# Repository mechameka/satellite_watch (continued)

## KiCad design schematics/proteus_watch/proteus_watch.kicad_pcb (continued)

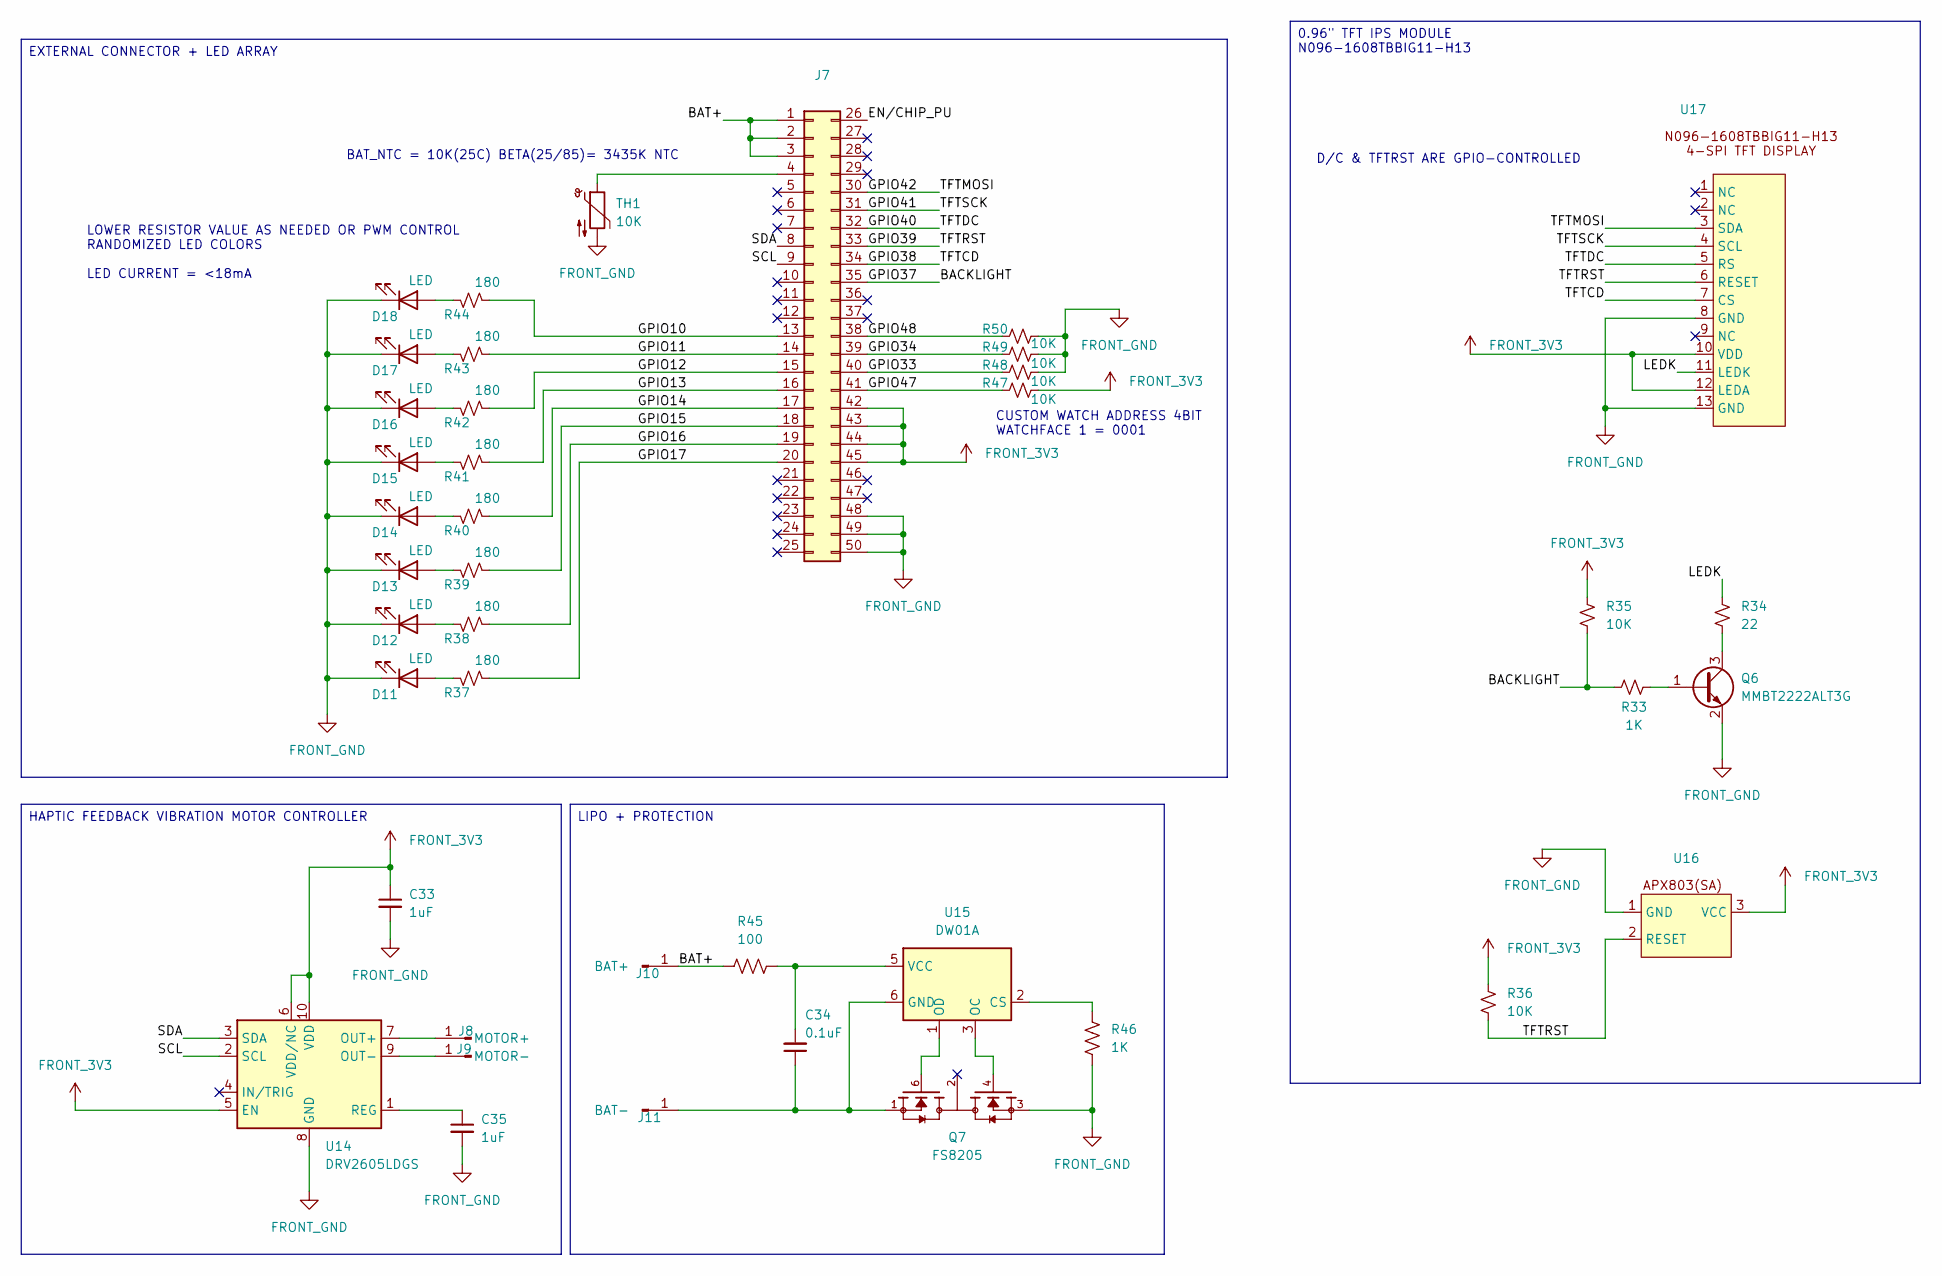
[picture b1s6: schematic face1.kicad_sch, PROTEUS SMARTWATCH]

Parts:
C33, C35: 1uF; C_0402_1005Metric_Pad0.74x0.62mm_HandSolder
C34: 0.1uF; C_0402_1005Metric_Pad0.74x0.62mm_HandSolder
D11, D12, D13, D14, D15, D16, D17, D18: LED; LED_1206_3216Metric_Pad1.42x1.75mm_HandSolder
J7: 2167010509_MOLEX; CON_2167010509_MOL
J8: MOTOR+; SolderWirePad_1x01_SMD_3x6mm
J9: MOTOR-; SolderWirePad_1x01_SMD_3x6mm
J10: BAT+; SolderWirePad_1x01_SMD_3x6mm
J11: BAT-; SolderWirePad_1x01_SMD_3x6mm
Q6: MMBT2222ALT3G; SOT-23
Q7: FS8205; SOT95P280X145-6N; PARTREV 1.9
R33, R46: 1K; R_0402_1005Metric_Pad0.72x0.64mm_HandSolder
R34: 22; R_0402_1005Metric_Pad0.72x0.64mm_HandSolder
R35, R36, R47, R48, R49, R50: 10K; R_0402_1005Metric_Pad0.72x0.64mm_HandSolder
R37, R38, R39, R40, R41, R42, R43, R44: 180; R_0402_1005Metric_Pad0.72x0.64mm_HandSolder
R45: 100; R_0402_1005Metric_Pad0.72x0.64mm_HandSolder
TH1: 10K; R_0402_1005Metric_Pad0.72x0.64mm_HandSolder
U14: DRV2605LDGS; TSSOP-10_3x3mm_P0.5mm
U15: DW01A; SOT-23-6
U16: SOT-23
U17: Wisevision N096-1608TBBIG11-H13

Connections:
/face1/BACKLIGHT: J7.35, R33.1, R35.1
/face1/BAT+: J7.1, J7.2, J7.3, J10.1 (Pin_1_1), R45.1
/face1/EN/CHIP_PU: J7.26
/face1/GPIO10: J7.13, R44.2
/face1/GPIO11: J7.14, R43.2
/face1/GPIO12: J7.15, R42.2
/face1/GPIO13: J7.16, R41.2
/face1/GPIO14: J7.17, R40.2
/face1/GPIO15: J7.18, R39.2
/face1/GPIO16: J7.19, R38.2
/face1/GPIO17: J7.20, R37.2
/face1/GPIO33: J7.40, R48.1
/face1/GPIO34: J7.39, R49.1
/face1/GPIO38: J7.34, U17.7 (CS)
/face1/GPIO39: J7.33, R36.1, U16.2 (RESET), U17.6 (RESET)
/face1/GPIO40: J7.32, U17.5 (RS)
/face1/GPIO41: J7.31, U17.4 (SCL)
/face1/GPIO42: J7.30, U17.3 (SDA)
/face1/GPIO47: J7.41, R47.1
/face1/GPIO48: J7.38, R50.1
/face1/LEDK: R34.2, U17.11 (LEDK)
/face1/SCL: J7.9, U14.2 (SCL)
/face1/SDA: J7.8, U14.3 (SDA)
FRONT_3V3: C33.1, J7.42, J7.43, J7.44, J7.45, R35.2, R36.2, R47.2, U14.5 (EN), U14.6 (VDD/NC), U14.10 (VDD), U16.3 (VCC), U17.10 (VDD), U17.12 (LEDA)
FRONT_GND: C33.2, C35.2, D11.1 (K), D12.1 (K), D13.1 (K), D14.1 (K), D15.1 (K), D16.1 (K), D17.1 (K), D18.1 (K), J7.48, J7.49, J7.50, Q6.2 (E), Q7.3, R46.1, R48.2, R49.2, R50.2, TH1.2, U14.8 (GND), U16.1 (GND), U17.8 (GND), U17.13 (GND)
unnamed: D11.2 (A), R37.1
unnamed: D12.2 (A), R38.1
unnamed: D13.2 (A), R39.1
unnamed: D14.2 (A), R40.1
unnamed: D15.2 (A), R41.1
unnamed: D16.2 (A), R42.1
unnamed: D17.2 (A), R43.1
unnamed: D18.2 (A), R44.1
unnamed: J7.4, TH1.1
unnamed: J8.1 (Pin_1_1), U14.7 (OUT+)
unnamed: J9.1 (Pin_1_1), U14.9 (OUT-)
unnamed: C34.1, J11.1 (Pin_1_1), Q7.1, U15.6 (GND)
unnamed: Q6.1 (B), R33.2
unnamed: Q6.3 (C), R34.1
unnamed: C35.1, U14.1 (REG)
unnamed: R46.2, U15.2 (CS)
unnamed: Q7.4, U15.3 (OC)
unnamed: Q7.6, U15.1 (OD)
unnamed: C34.2, R45.2, U15.5 (VCC)

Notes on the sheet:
BAT_NTC = 10K(25C) BETA(25/85)= 3435K NTC
D/C & TFTRST ARE GPIO-CONTROLLED
CUSTOM WATCH ADDRESS 4BIT WATCHFACE 1 = 0001
LOWER RESISTOR VALUE AS NEEDED OR PWM CONTROL RANDOMIZED LED COLORS LED CURRENT = <18mA
LIPO + PROTECTION
HAPTIC FEEDBACK VIBRATION MOTOR CONTROLLER
0.96" TFT IPS MODULE N096-1608TBBIG11-H13
EXTERNAL CONNECTOR + LED ARRAY

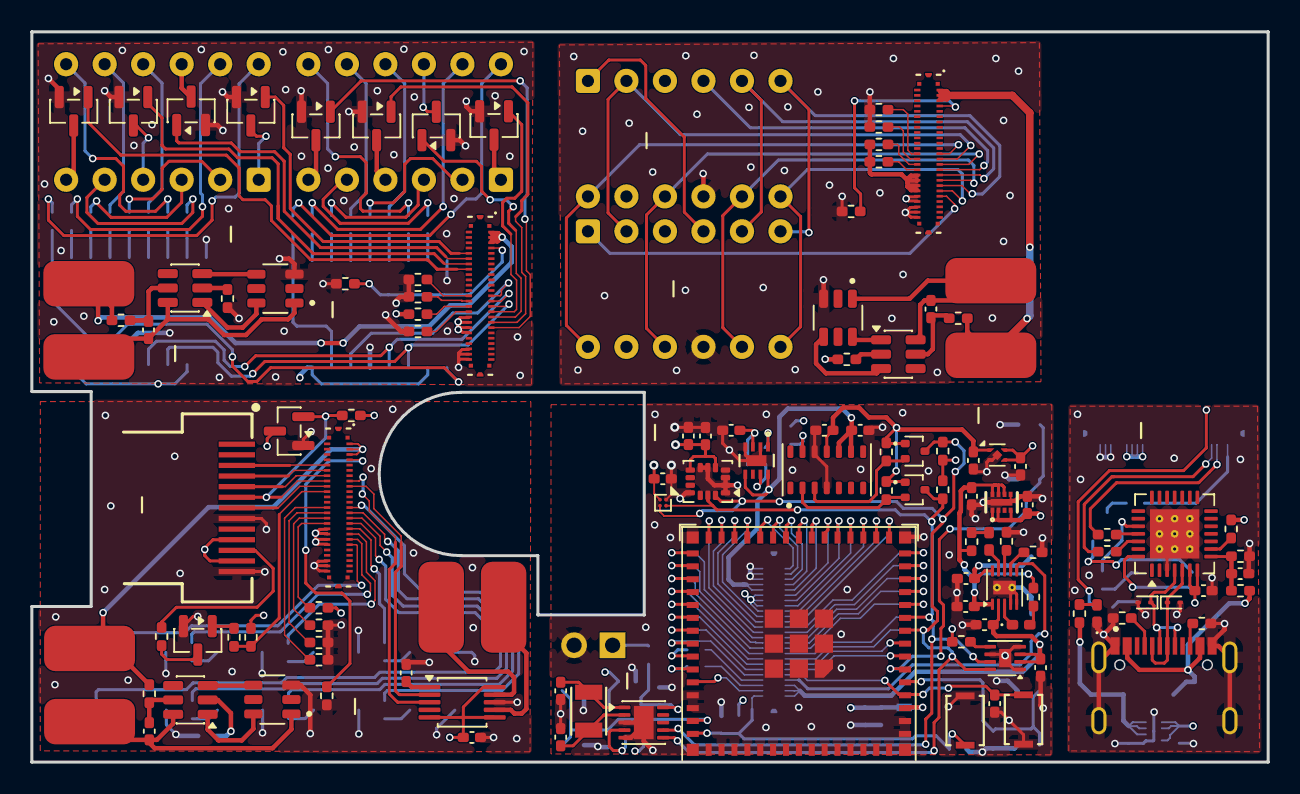
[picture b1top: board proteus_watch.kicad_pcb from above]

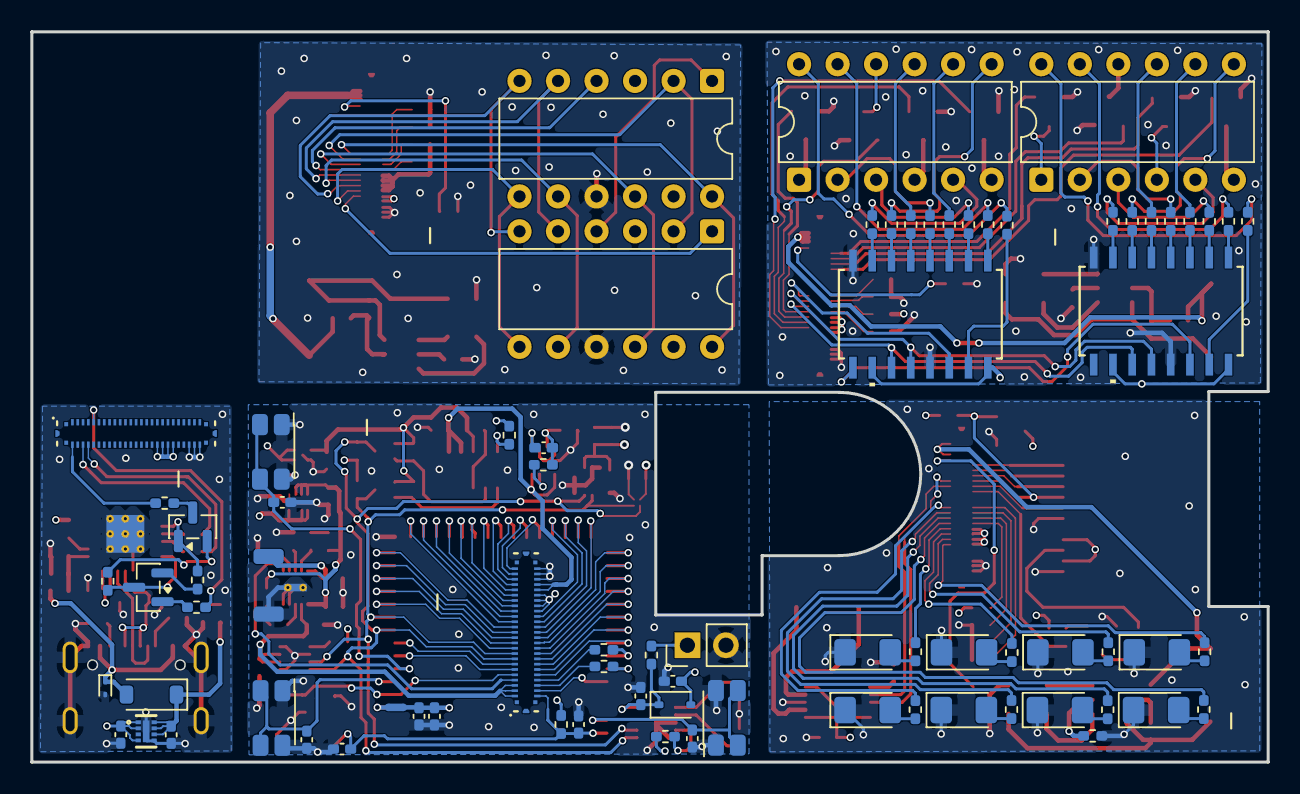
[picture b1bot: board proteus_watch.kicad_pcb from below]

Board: 4 copper layers, 81.5 x 48.2 mm, 193 parts (77 on the bottom side), 223 nets.

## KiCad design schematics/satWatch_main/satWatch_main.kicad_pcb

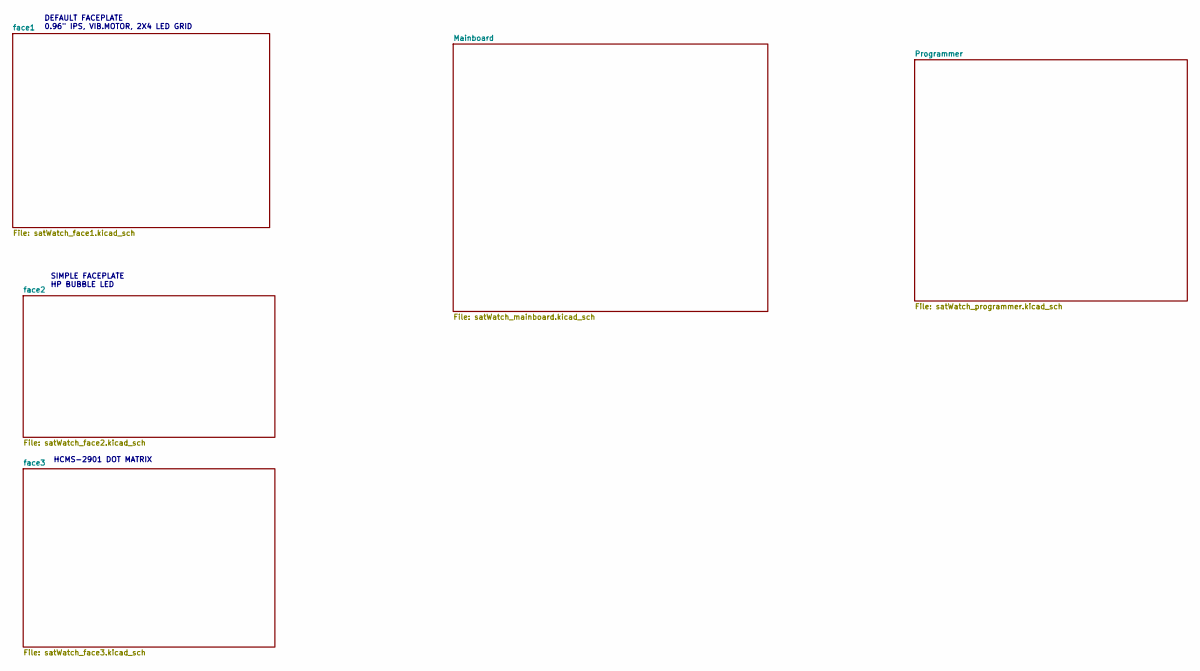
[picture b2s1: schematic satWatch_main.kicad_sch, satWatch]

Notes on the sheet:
HCMS-2901 DOT MATRIX
SIMPLE FACEPLATE HP BUBBLE LED
DEFAULT FACEPLATE 0.96" IPS, VIB.MOTOR, 2X4 LED GRID

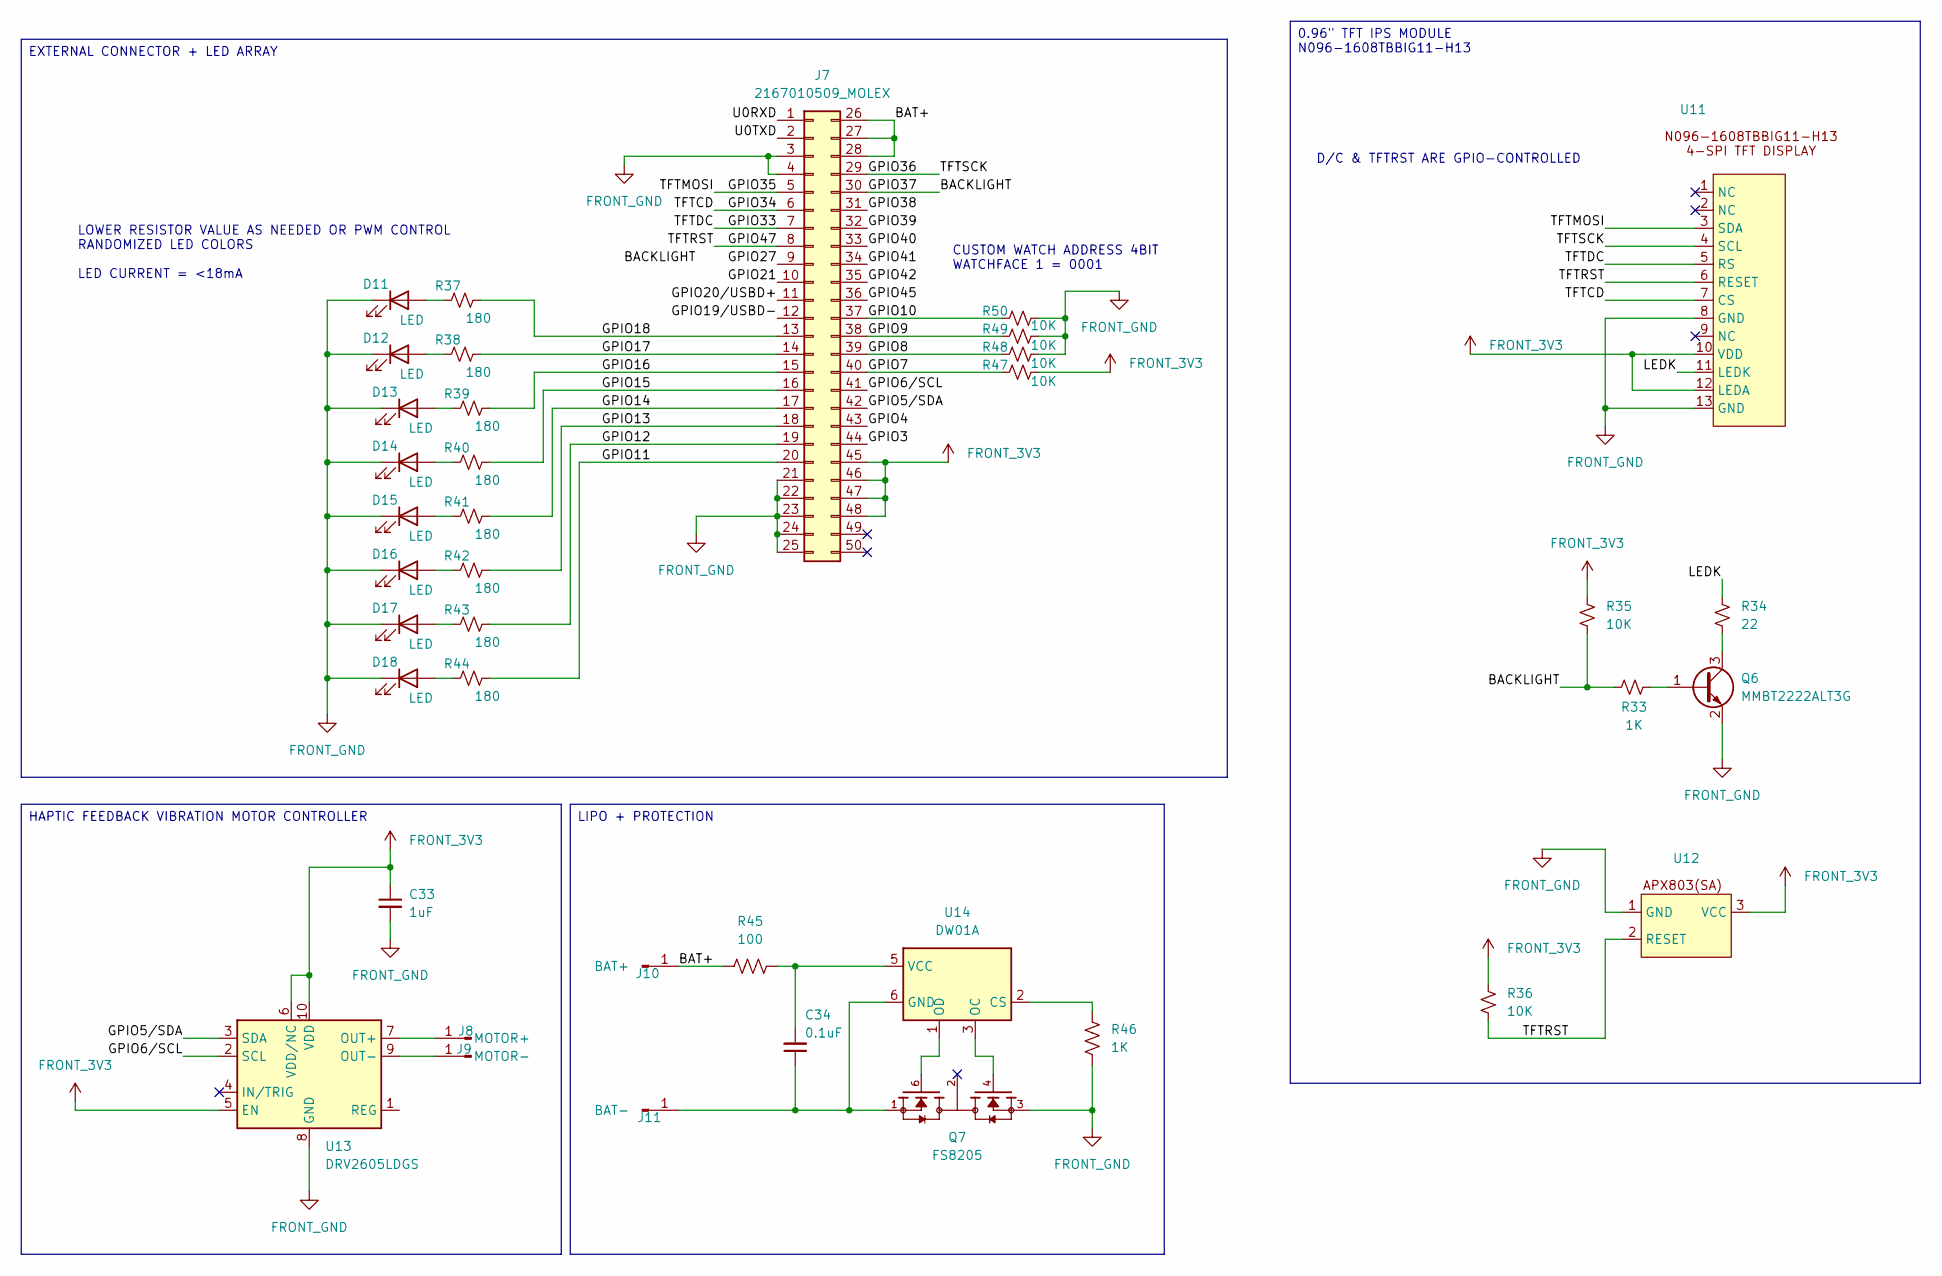
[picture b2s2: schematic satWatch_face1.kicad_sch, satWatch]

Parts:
C33: 1uF; C_0402_1005Metric_Pad0.74x0.62mm_HandSolder
C34: 0.1uF; C_0402_1005Metric_Pad0.74x0.62mm_HandSolder
D11, D12, D13, D14, D15, D16, D17, D18: LED; LED_1206_3216Metric_Pad1.42x1.75mm_HandSolder
J7: 2167010509_MOLEX; CON_2167010509_MOL
J8: MOTOR+; SolderWirePad_1x01_SMD_3x6mm
J9: MOTOR-; SolderWirePad_1x01_SMD_3x6mm
J10: BAT+; SolderWirePad_1x01_SMD_3x6mm
J11: BAT-; SolderWirePad_1x01_SMD_3x6mm
Q6: MMBT2222ALT3G; SOT-23
Q7: FS8205; SOT95P280X145-6N; PARTREV 1.9
R33, R46: 1K; R_0402_1005Metric_Pad0.72x0.64mm_HandSolder
R34: 22; R_0402_1005Metric_Pad0.72x0.64mm_HandSolder
R35, R36, R47, R48, R49, R50: 10K; R_0402_1005Metric_Pad0.72x0.64mm_HandSolder
R37, R38, R39, R40, R41, R42, R43, R44: 180; R_0402_1005Metric_Pad0.72x0.64mm_HandSolder
R45: 100; R_0402_1005Metric_Pad0.72x0.64mm_HandSolder
U11: Wisevision N096-1608TBBIG11-H13
U12: SOT-23
U13: DRV2605LDGS; TSSOP-10_3x3mm_P0.5mm
U14: DW01A; SOT-23-6

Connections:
/face1/BACKLIGHT: J7.30, R33.1, R35.1
/face1/BAT+: J7.26, J7.27, J7.28, J10.1 (Pin_1_1), R45.1
/face1/GPIO3: J7.44
/face1/GPIO4: J7.43
/face1/GPIO5/SDA: J7.42, U13.3 (SDA)
/face1/GPIO6/SCL: J7.41, U13.2 (SCL)
/face1/GPIO7: J7.40, R47.1
/face1/GPIO8: J7.39, R48.1
/face1/GPIO9: J7.38, R49.1
/face1/GPIO10: J7.37, R50.1
/face1/GPIO11: J7.20, R44.2
/face1/GPIO12: J7.19, R43.2
/face1/GPIO13: J7.18, R42.2
/face1/GPIO14: J7.17, R41.2
/face1/GPIO15: J7.16, R40.2
/face1/GPIO16: J7.15, R39.2
/face1/GPIO17: J7.14, R38.2
/face1/GPIO18: J7.13, R37.2
/face1/GPIO19/USBD-: J7.12
/face1/GPIO20/USBD+: J7.11
/face1/GPIO21: J7.10
/face1/GPIO27: J7.9
/face1/GPIO33: J7.7, U11.5 (RS)
/face1/GPIO34: J7.6, U11.7 (CS)
/face1/GPIO35: J7.5, U11.3 (SDA)
/face1/GPIO36: J7.29, U11.4 (SCL)
/face1/GPIO38: J7.31
/face1/GPIO39: J7.32
/face1/GPIO40: J7.33
/face1/GPIO41: J7.34
/face1/GPIO42: J7.35
/face1/GPIO45: J7.36
/face1/GPIO47: J7.8, R36.1, U11.6 (RESET), U12.2 (RESET)
/face1/LEDK: R34.2, U11.11 (LEDK)
/face1/U0RXD: J7.1
/face1/U0TXD: J7.2
FRONT_3V3: C33.1, J7.45, J7.46, J7.47, J7.48, R35.2, R36.2, R47.2, U11.10 (VDD), U11.12 (LEDA), U12.3 (VCC), U13.5 (EN), U13.6 (VDD/NC), U13.10 (VDD); also elsewhere on the board
FRONT_GND: C33.2, D11.1 (K), D12.1 (K), D13.1 (K), D14.1 (K), D15.1 (K), D16.1 (K), D17.1 (K), D18.1 (K), J7.3, J7.4, J7.21, J7.22, J7.23, J7.24, J7.25, Q6.2 (E), Q7.3, R46.1, R48.2, R49.2, R50.2, U11.8 (GND), U11.13 (GND), U12.1 (GND), U13.8 (GND); also elsewhere on the board
unnamed: D11.2 (A), R37.1
unnamed: D12.2 (A), R38.1
unnamed: D13.2 (A), R39.1
unnamed: D14.2 (A), R40.1
unnamed: D15.2 (A), R41.1
unnamed: D16.2 (A), R42.1
unnamed: D17.2 (A), R43.1
unnamed: D18.2 (A), R44.1
unnamed: J8.1 (Pin_1_1), U13.7 (OUT+)
unnamed: J9.1 (Pin_1_1), U13.9 (OUT-)
unnamed: C34.1, J11.1 (Pin_1_1), Q7.1, U14.6 (GND)
unnamed: Q6.1 (B), R33.2
unnamed: Q6.3 (C), R34.1
unnamed: R46.2, U14.2 (CS)
unnamed: Q7.4, U14.3 (OC)
unnamed: Q7.6, U14.1 (OD)
unnamed: C34.2, R45.2, U14.5 (VCC)

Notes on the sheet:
CUSTOM WATCH ADDRESS 4BIT WATCHFACE 1 = 0001
LOWER RESISTOR VALUE AS NEEDED OR PWM CONTROL RANDOMIZED LED COLORS LED CURRENT = <18mA
D/C & TFTRST ARE GPIO-CONTROLLED
LIPO + PROTECTION
EXTERNAL CONNECTOR + LED ARRAY
0.96" TFT IPS MODULE N096-1608TBBIG11-H13
HAPTIC FEEDBACK VIBRATION MOTOR CONTROLLER

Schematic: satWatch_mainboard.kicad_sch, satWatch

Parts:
BT1: 2895 (CR1220 Holder); BAT_2895; PARTREV B
C1, C3, C31, C32: 1uF; C_0402_1005Metric_Pad0.74x0.62mm_HandSolder
C2, C10, C17, C30: 10uF; C_0402_1005Metric_Pad0.74x0.62mm_HandSolder
C4: 22uF; C_0402_1005Metric_Pad0.74x0.62mm_HandSolder
C5, C7: 1uF/16V(10%); C_0402_1005Metric_Pad0.74x0.62mm_HandSolder
C6: 10uF/16V(10%); C_0402_1005Metric_Pad0.74x0.62mm_HandSolder
C8, C9, C11, C13, C14: 0.1uF/50V(10%); C_0402_1005Metric_Pad0.74x0.62mm_HandSolder
C12, C15, C16, C19, C29: 0.1uF; C_0402_1005Metric_Pad0.74x0.62mm_HandSolder
C18, C20: 22pF; C_0402_1005Metric_Pad0.74x0.62mm_HandSolder
C37: 1uF/6.3V; C_0402_1005Metric_Pad0.74x0.62mm_HandSolder
C38: 10uF/6.3V; C_0402_1005Metric_Pad0.74x0.62mm_HandSolder
D1: SDB14HS-AQ; D_SOD-323_HandSoldering
D8: DONE; LED_0402_1005Metric_Pad0.77x0.64mm_HandSolder
D9: CHRG; LED_0402_1005Metric_Pad0.77x0.64mm_HandSolder
D10: RED; LED_0402_1005Metric_Pad0.77x0.64mm_HandSolder
J1: 2167010509_MOLEX; CON_2167010509_MOL
J2: Pogo_02x03_UARTPROG; CUSTOM_POGO_02X03
J5, J6: SOLDER POINT; SolderWire-0.25sqmm_1x01_D0.65mm_OD1.7mm
L1: 2.2Uh; L_0402_1005Metric_Pad0.77x0.64mm_HandSolder
Q1: DMP1045U; SOT-23-3; PARTREV 7 - 2
Q2, Q3: RE1C002UN; SOT-416
R1, R14: 10K; R_0402_1005Metric_Pad0.72x0.64mm_HandSolder
R2: 100K; R_0402_1005Metric_Pad0.72x0.64mm_HandSolder
R3: 750K; R_0402_1005Metric_Pad0.72x0.64mm_HandSolder
R4, R8, R11, R13: 2.2K; R_0402_1005Metric_Pad0.72x0.64mm_HandSolder
R5: 10K(1%); R_0402_1005Metric_Pad0.72x0.64mm_HandSolder
R6: 499; R_0402_1005Metric_Pad0.72x0.64mm_HandSolder
R7, R9: 0; R_0402_1005Metric_Pad0.72x0.64mm_HandSolder
R10, R12: 220K; R_0402_1005Metric_Pad0.72x0.64mm_HandSolder
R15: 4.7K; R_0402_1005Metric_Pad0.72x0.64mm_HandSolder
R29, R30: 1K; R_0402_1005Metric_Pad0.72x0.64mm_HandSolder
R31: 1.2k; R_0402_1005Metric_Pad0.72x0.64mm_HandSolder
R32: 5.1K(1%); R_0402_1005Metric_Pad0.72x0.64mm_HandSolder
SW1, SW2: R-667995; R-667995_MIT-L
SW3, SW4, SW5: EVQ-P7A01P; SW_SPST_EVQP7A
U1: PAM2401SCADJ; MSOP8_DIO
U2: MIC5365-1.8YC5; SOT-353_SC-70-5
U3: ESP32-S3-MINI-1
U4: MAX30101EFD_T; MAX30101EFD+T; PARTREV 2
U5: BNO085; IC_BNO085; PARTREV v1.17
U6: DS3231MZ; SOIC-8_3.9x4.9mm_P1.27mm
U9: TP4056-42-ESOP8; SOIC-8-1EP_3.9x4.9mm_P1.27mm_EP2.41x3.3mm_ThermalVias
U10: NCP186AMX330TAG; PSON40P160X120X45-9N; PARTREV Rev.5
U21: ADP5063; QFN-20-1EP_4x4mm_P0.5mm_EP2.5x2.5mm
U22: AXP2101; QFN-40-1EP_5x5mm_P0.4mm_EP3.6x3.6mm_ThermalVias
Y1: 32.768Hz; ABS07-32.768KHZ-T

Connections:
1V8: C3.1, C12.1, Q2.1 (G), Q3.1 (G), R4.1, R11.1, U2.5 (VOUT), U4.11 (VDD)
3V3: C1.1, C2.1, C5.1, C6.1, C16.1, C17.1, C19.1, D1.1 (K), J1.45, J1.46, J1.47, J1.48, L1.1, Q1.2, R5.1, R8.1, R13.1, R14.1, R15.2, U1.2 (EN), U1.3 (VIN), U2.1 (VIN), U2.3 (EN), U3.3 (3V3), U5.3 (VDD), U5.11 (~RST), U5.28 (VDDIO), U6.2 (VCC)
5V: C4.1, C10.2, J1.49, J1.50, R3.2, U1.7 (OUT), U4.9 (VLED+), U4.10 (VLED+__1)
/Mainboard/BAT+: C30.1, J1.26, J1.27, J1.28, Q1.3, R10.2, U9.5 (BAT)
/Mainboard/BATTERY_MONITOR: R9.1, U3.30 (IO48)
/Mainboard/EN/CHIP_PU: C7.1, C9.1, J2.3, R5.2, SW2.2, U3.45 (EN)
/Mainboard/GPIO0/BOOT: C8.1, J2.6, SW1.2, U3.4 (IO0)
/Mainboard/GPIO1/BUTTON1: C11.1, SW3.2, U3.5 (IO1)
/Mainboard/GPIO2/BUTTON3: C14.1, SW5.2, U3.6 (IO2)
/Mainboard/GPIO3: J1.44, U3.7 (IO3)
/Mainboard/GPIO4: J1.43, U3.8 (IO4)
/Mainboard/GPIO5/SDA: J1.42, Q3.3 (D), R13.2, U3.9 (IO5), U5.20 (H_SDA/H_MISO/TX), U6.7 (SDA)
/Mainboard/GPIO6/SCL: J1.41, Q2.3 (D), R8.2, U3.10 (IO6), U5.19 (H_SCL/SCK/RX), U6.8 (SCL)
/Mainboard/GPIO7: J1.40, U3.11 (IO7)
/Mainboard/GPIO8: J1.39, U3.12 (IO8)
/Mainboard/GPIO9: J1.38, U3.13 (IO9)
/Mainboard/GPIO10: J1.37, U3.14 (IO10)
/Mainboard/GPIO11: J1.20, U3.15 (IO11)
/Mainboard/GPIO12: J1.19, U3.16 (IO12)
/Mainboard/GPIO13: J1.18, U3.17 (IO13)
/Mainboard/GPIO14: J1.17, U3.18 (IO14)
/Mainboard/GPIO15: J1.16, U3.19 (IO15)
/Mainboard/GPIO16: J1.15, U3.20 (IO16)
/Mainboard/GPIO17: J1.14, U3.21 (IO17)
/Mainboard/GPIO18: J1.13, U3.22 (IO18)
/Mainboard/GPIO19/USBD-: J1.12, U3.23 (USB_D-)
/Mainboard/GPIO20/USBD+: J1.11, U3.24 (USB_D+)
/Mainboard/GPIO21: J1.10, U3.25 (IO21)
/Mainboard/GPIO27: J1.9, U3.26 (IO26)
/Mainboard/GPIO33: J1.7, U3.28 (IO33)
/Mainboard/GPIO34: J1.6, U3.29 (IO34)
/Mainboard/GPIO35: J1.5, U3.31 (IO35)
/Mainboard/GPIO36: J1.29, U3.32 (IO36)
/Mainboard/GPIO37: J1.30, U3.33 (IO37)
/Mainboard/GPIO38: J1.31, U3.34 (IO38)
/Mainboard/GPIO39: J1.32, U3.35 (IO39)
/Mainboard/GPIO40: J1.33, U3.36 (IO40)
/Mainboard/GPIO41: J1.34, U3.37 (IO41)
/Mainboard/GPIO42: J1.35, U3.38 (IO42)
/Mainboard/GPIO45: J1.36, U3.41 (IO45)
/Mainboard/GPIO46/BUTTON2: C13.1, SW4.2, U3.44 (IO46)
/Mainboard/GPIO47: J1.8, U3.27 (IO47)
/Mainboard/LV_SCL: Q2.2 (S), R4.2, U4.2 (SCL)
/Mainboard/LV_SDA: Q3.2 (S), R11.2, U4.3 (SDA)
/Mainboard/U0RXD: J1.1, J2.4, R7.2
/Mainboard/U0TXD: J1.2, J2.5, R6.2
/Mainboard/VDOCK_5V: C29.1, C31.1, D8.2 (A), D9.2 (A), J5.1 (Pin_1_1), U9.4 (V_{CC}), U9.8 (CE), U10.6 (EN), U10.7 (IN), U10.8 (IN__1)
GND: BT1.N, C1.2, C2.2, C3.2, C4.2, C5.2, C6.2, C7.2, C8.2, C9.2, C10.1, C11.2, C12.2, C13.2, C14.2, C15.2, C16.2, C17.2, C18.2, C19.2, C20.2, C29.2, C30.2, C31.2, C32.2, C37.1, C38.1, D10.1 (K), J1.3, J1.4, J1.21, J1.22, J1.23, J1.24, J1.25, J2.2, J6.1 (Pin_1_1), R1.2, R2.2, R12.2, R31.2, SW1.1, SW2.1, SW3.1, SW4.1, SW5.1, U1.4 (AGND), U1.8 (PGND), U2.2 (GND), U3.1 (GND), U3.2 (GND), U3.42 (GND), U3.43 (GND), U3.46 (GND), U3.47 (GND), U3.48 (GND), U3.49 (GND), U3.50 (GND), U3.51 (GND), U3.52 (GND), U3.53 (GND), U3.54 (GND), U3.55 (GND), U3.56 (GND), U3.57 (GND), U3.58 (GND), U3.59 (GND), U3.60 (GND), U3.61 (GND), U3.62 (GND), U3.63 (GND), U3.64 (GND), U3.65 (GND), U4.4 (PGND), U4.12 (GND), U5.2 (GND), U5.5 (PS1), U5.6 (PS0/WAKE), U5.10 (CLKSEL0), U5.17 (SA0/H_MOSI), U5.18 (~H_CS), U5.25 (GNDIO), U6.5 (GND), U9.1 (TEMP), U9.3 (GND), U9.9 (EPAD), U10.5 (GND), U10.9 (EPAD), U22.3 (GND), U22.40 (SCK)
unnamed: C37.2, U22.2 (VREF)
unnamed: C38.2, U22.37 (VBUS)
unnamed: D8.1 (K), R29.1
unnamed: D9.1 (K), R30.1
unnamed: D10.2 (A), R32.2
unnamed: R9.2, R10.1, R12.1
unnamed: R2.1, R3.1, U1.5 (FB)
unnamed: L1.2, U1.1 (LX)
unnamed: R7.1, U3.40 (RXD0)
unnamed: R6.1, U3.39 (TXD0)
unnamed: R15.1, U4.13 (~INT)
unnamed: C15.1, U5.9 (CAP)
unnamed: C20.1, U5.27 (XIN32), Y1.1
unnamed: C18.1, U5.26 (XOUT32/CLKSEL1), Y1.2
unnamed: R14.2, U5.4 (~BOOT)
unnamed: BT1.P1, BT1.P2, U6.6 (VBAT)
unnamed: R31.1, U9.2 (PROG)
unnamed: R30.2, U9.7 (~CHRG)
unnamed: R29.2, U9.6 (~STDBY)
unnamed: U21.6 (VINx), U21.7 (VINx), U21.8 (VINx)
unnamed: U21.9 (ISO_Sx), U21.10 (ISO_Sx), U21.11 (ISO_Sx)
unnamed: U21.12 (ISO_Bx), U21.13 (ISO_Bx), U21.14 (ISO_Bx)
VIN_3V3: C32.1, D1.2 (A), J2.1, Q1.1, R1.1, R32.1, U10.1 (OUT), U10.2 (OUT__1), U10.4 (FB/ADJ)

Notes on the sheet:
MOUNTS TO AN EXTERNAL CHARGING DOCK BATTERY OVERCHARGE/DISCHARGE (DW01A) TYPICALLY INCLUDED IN FACEPLATE 1000mAh/1A
SWITCHES BETWEEN FRONT PANEL POWER AND PROGRAMMER-SUPPLIED POWER
POPULATE ONLY FOR DOCKUNIT SETUP
NMOSFET: Vth > 1.2V Vgs (TYP. 0.6V BODY DIODE VOLT DIFF) RE1C002UN = 1V Vth
1X ON SIDE // 2X ON OTHER SIDE TYP. WAKE,SELECT,MENU / UP / DOWN
3.3V REGULATOR OUTPUT CURRENT: 1A QUIESCENT CURRENT: 140uA
DC-DC CONVERTER TO 5V FOR MAX30101 INPUT: 2.4-4.75V
REFERENCE DESIGN FROM SPARKFUN MAX30101 QWIC TYPICAL CURRENT CONSUMPTION 600-1000uA VCC RANGE: 1.7 - 2.0V VCC RED/IR LED: 3.1-5.0V VCC GREN LED: 4.5-5.5V I2C ADD: 0X57
I2C ADD: 0X4A (SA0 PULLED TO 0) RESET CONTROL DISABLED (PULLED HIGH)
1.8V REGULATOR OUTPUT CURRENT: 150mA QUIESCENT CURRENT: 29uA
PROGRAMMABLE BUTTONS
POWER LOAD SHARING PROTECTION
POWER REGULATION
PULSE OXIMETER AND HEART RATE SENSOR
EXTERNAL CONNECTORS
9AXIS IMU BNO085
**DOCK CONFIGURATION**
ESP32-S3-MINI-1
RTC CLOCK
LIPO BATTERY CHARGER
DIAGNOSTIC BUTTONS
PULLUPS / LEVEL SHIFTER
WATCHBODY CONFIGURATION

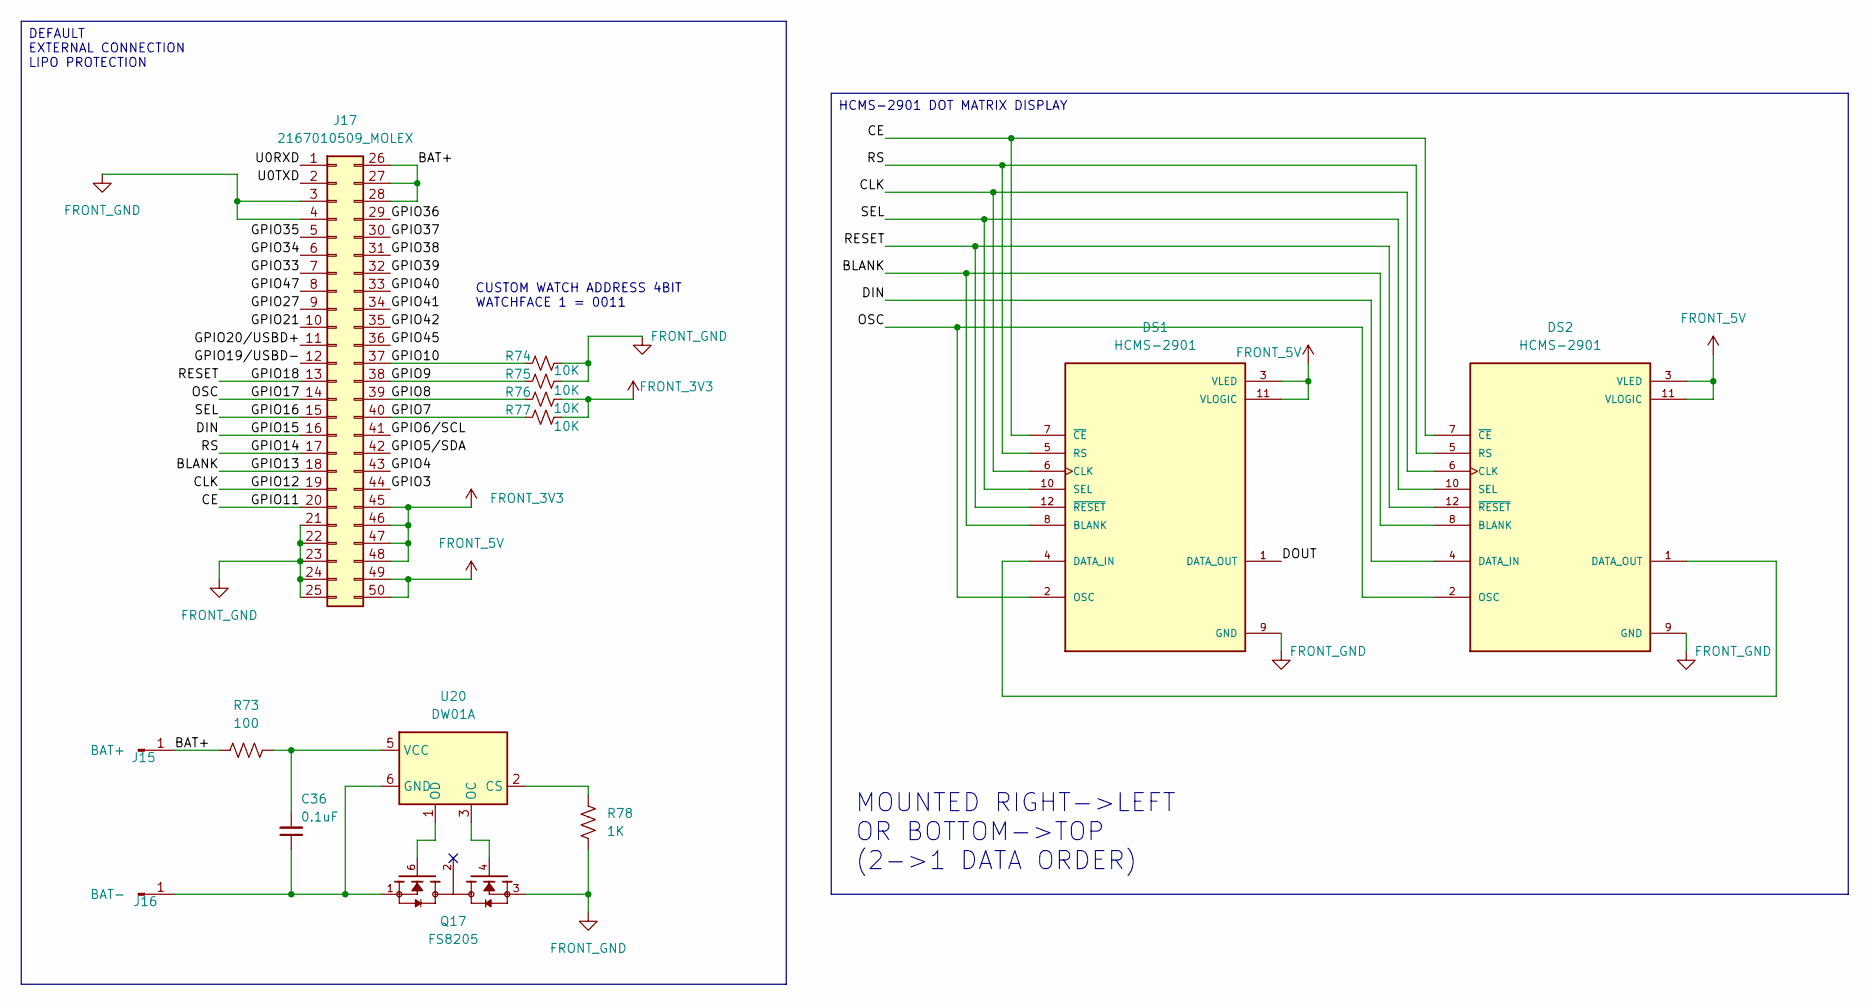
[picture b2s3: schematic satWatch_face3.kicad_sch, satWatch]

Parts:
C36: 0.1uF; C_0402_1005Metric_Pad0.74x0.62mm_HandSolder
DS1, DS2: HCMS-2901; DIP-12_W7.62mm; PARTREV N/A
J15: BAT+; SolderWirePad_1x01_SMD_3x6mm
J16: BAT-; SolderWirePad_1x01_SMD_3x6mm
J17: 2167010509_MOLEX; CON_2167010509_MOL
Q17: FS8205; SOT95P280X145-6N; PARTREV 1.9
R73: 100; R_0402_1005Metric_Pad0.72x0.64mm_HandSolder
R74, R75, R76, R77: 10K; R_0402_1005Metric_Pad0.72x0.64mm_HandSolder
R78: 1K; R_0402_1005Metric_Pad0.72x0.64mm_HandSolder
U20: DW01A; SOT-23-6

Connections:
/face3/BAT+: J15.1 (Pin_1_1), J17.26, J17.27, J17.28, R73.1
/face3/BLANK: DS1.8 (BLANK), DS2.8 (BLANK), J17.18
/face3/CE: DS1.7 (~CE), DS2.7 (~CE), J17.20
/face3/CLK: DS1.6 (CLK), DS2.6 (CLK), J17.19
/face3/DIN: DS2.4 (DATA_IN), J17.16
/face3/DOUT: DS1.1 (DATA_OUT)
/face3/GPIO3: J17.44
/face3/GPIO4: J17.43
/face3/GPIO5/SDA: J17.42
/face3/GPIO6/SCL: J17.41
/face3/GPIO7: J17.40, R77.1
/face3/GPIO8: J17.39, R76.1
/face3/GPIO9: J17.38, R75.1
/face3/GPIO10: J17.37, R74.1
/face3/GPIO14: DS1.5 (RS), DS2.5 (RS), J17.17
/face3/GPIO16: DS1.10 (SEL), DS2.10 (SEL), J17.15
/face3/GPIO17: DS1.2 (OSC), DS2.2 (OSC), J17.14
/face3/GPIO18: DS1.12 (~RESET), DS2.12 (~RESET), J17.13
/face3/GPIO19/USBD-: J17.12
/face3/GPIO20/USBD+: J17.11
/face3/GPIO21: J17.10
/face3/GPIO27: J17.9
/face3/GPIO33: J17.7
/face3/GPIO34: J17.6
/face3/GPIO35: J17.5
/face3/GPIO36: J17.29
/face3/GPIO37: J17.30
/face3/GPIO38: J17.31
/face3/GPIO39: J17.32
/face3/GPIO40: J17.33
/face3/GPIO41: J17.34
/face3/GPIO42: J17.35
/face3/GPIO45: J17.36
/face3/GPIO47: J17.8
/face3/U0RXD: J17.1
/face3/U0TXD: J17.2
FRONT_3V3: J17.45, J17.46, J17.47, J17.48, R76.2, R77.2; also elsewhere on the board
FRONT_5V: DS1.3 (VLED), DS1.11 (VLOGIC), DS2.3 (VLED), DS2.11 (VLOGIC), J17.49, J17.50
FRONT_GND: DS1.9 (GND), DS2.9 (GND), J17.3, J17.4, J17.21, J17.22, J17.23, J17.24, J17.25, Q17.3, R74.2, R75.2, R78.1; also elsewhere on the board
unnamed: DS1.4 (DATA_IN), DS2.1 (DATA_OUT)
unnamed: C36.1, J16.1 (Pin_1_1), Q17.1, U20.6 (GND)
unnamed: R78.2, U20.2 (CS)
unnamed: Q17.4, U20.3 (OC)
unnamed: Q17.6, U20.1 (OD)
unnamed: C36.2, R73.2, U20.5 (VCC)

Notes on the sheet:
MOUNTED RIGHT->LEFT OR BOTTOM->TOP (2->1 DATA ORDER)
CUSTOM WATCH ADDRESS 4BIT WATCHFACE 1 = 0011
DEFAULT EXTERNAL CONNECTION LIPO PROTECTION
HCMS-2901 DOT MATRIX DISPLAY
